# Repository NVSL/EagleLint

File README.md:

# EagleLint

Eaglint is a style checker for Cadsoft Eagle PCB design files.

## Installation

```
$ cd EagleLint 
$ pip install .
```

This will install several libraries, the most important of which is `Swoop` a Python library for working with Eagle files.

## Test It

```
$ eaglelint --files tests/test.sch tests/test.brd test.lbr
```

It will print out some errors.

## Usage

Get help: `eaglelint --help`

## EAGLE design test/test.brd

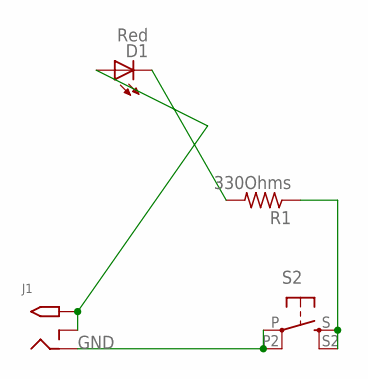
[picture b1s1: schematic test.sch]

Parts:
D1: Red; LED5MM
J1: 2.1MMJACKTHM; PJ-102A
R1: 330Ohms; RESAD1160W55L680D260_HS
S2: PUSH-BUTTON-SQUARE; BUTTON-TACTILE-SQUARE-ADAFRUIT1010

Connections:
5V: D1.A, J1.RING_SW, J1.TIP
GND: J1.RING, S2.P, S2.P2 (P1)
unnamed: D1.K (C), R1.2
unnamed: R1.1, S2.S, S2.S2 (S1)

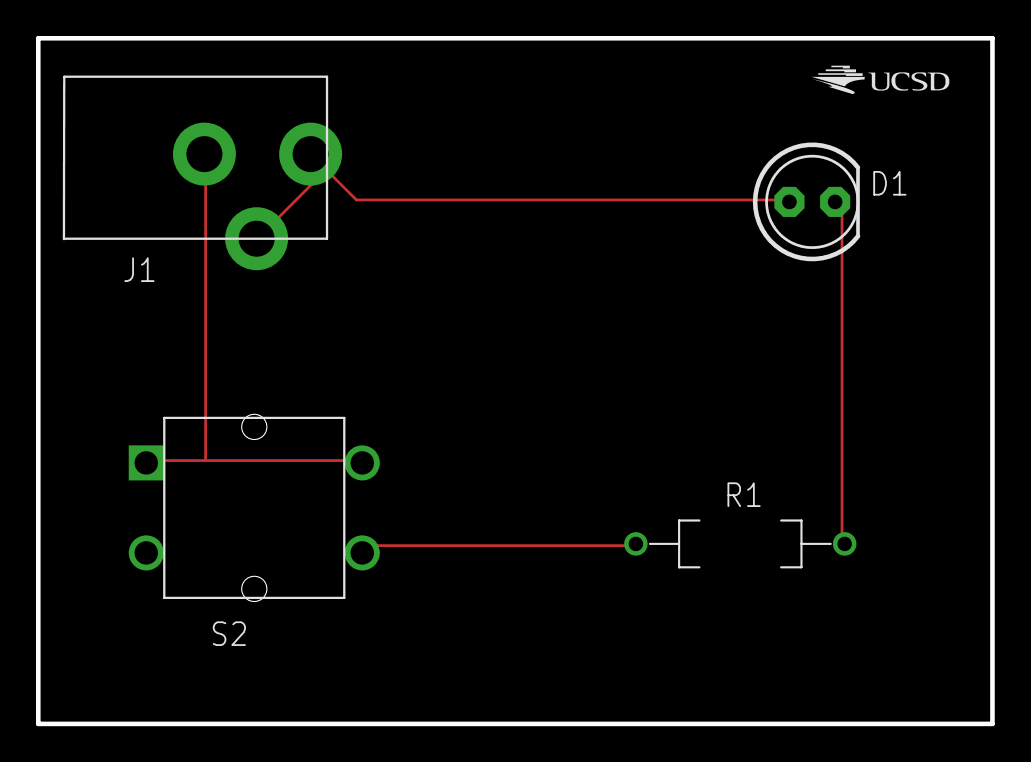
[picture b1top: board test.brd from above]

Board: 2 copper layers, 53.0 x 38.1 mm, 5 parts (0 on the bottom side), 4 nets.

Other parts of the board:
L1: UCSD_LOGO

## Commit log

2019-04-12 import files
2019-04-13 readme
2019-04-13 add some test files. Cleanup
2019-04-21 better error message
2019-04-26 adjust decoupling cap count. ADd check on via drill size
2019-04-30 Smarter checks for board outline. Check for non-zero isolate on pours
2019-05-03 better checks for attributes on board
2019-05-03 fix board outline guidance so they show up in cam files
2019-05-03 better bounding box tools
2019-05-13 fix case sensitivity it library lookup
2021-01-06 allow 0.5mm grid. Check for silly connections on two-terminal devices. Allow 'one of' constraints in patterns
2022-01-06 changes from last year. Disable some checks due to fusion360
